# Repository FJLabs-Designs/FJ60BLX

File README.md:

# FJ60BLX Bluetooth 60% Mechanical Keyboard PCB

The following repository will hold the design files of the FJ60BLX Bluetooth Mechanical Keyboard PCB. This is designed to be a living repository and design files in this repository will be continually updated as the board iterates and changes.

## About this Repository

This repository contains rolling updates to the FJ60BLX Bluetooth PCB. Included are the base Eagle files (Board File, Schematic, and CAM Processor Job), the associated Gerber files for that revision, and the associated Bills of Materials. Each of these files will be segregated into their respective versions that are date-coded with the day of export. 

## Eagle Files

The core of this repository are the bare Eagle files. These files are the basis for the Gerber exports. **When using the eagle files, please remove the FJLabs and FJ60BLX branding.**

## Gerber Files

Included are the Gerber Files for manufacturing. These should be available in 5.6 format for all copper layers, and 4.5 format for all drills. Your PCB manufacturer requires these files to create the PCB itself. Additionally, included in the Gerber files are the relevant Pick and Place Coordinate/Centroid files which are needed for PCBA. 

## BOM Files

The included BOM files are available as Excel spreadsheets with LCSC links whereever possible. Certain components are not available from LCSC and must be purchased either directly from the manufacturer or from an authorized components distributor. 

## Renders

This folder includes a master list of all renders that have been sent to subscribers of the FJ60BLX mailing list and are date-coded. 

## Manufacturing Information

### Bluetooth Module

The PCB uses the MDBT40-256v3 Bluetooth module designed and manufactured by Raytac. This module must be programmed with the Adafruit Bluefruit SPI Friend firmware for compatibility with QMK. The relevant firmware has not been included as it is property of Adafruit and its respective company. However, this firmware is available for free open-source on GitHub (link not provided). Additionally, a SoftDevice file is required for programming of the bare Bluetooth module, which is included in the Adafruit repository for the Nordic 51822 chipset. 

Instructions are not included for programming the Bluetooth module over SWD, as it is more productive to purchase such modules pre-programmed directly from the manufacturer. The difference in cost between a programmed and unprogrammed module is negligble and therefore, for production, it is *highly recommended* to purchase preflashed chips.

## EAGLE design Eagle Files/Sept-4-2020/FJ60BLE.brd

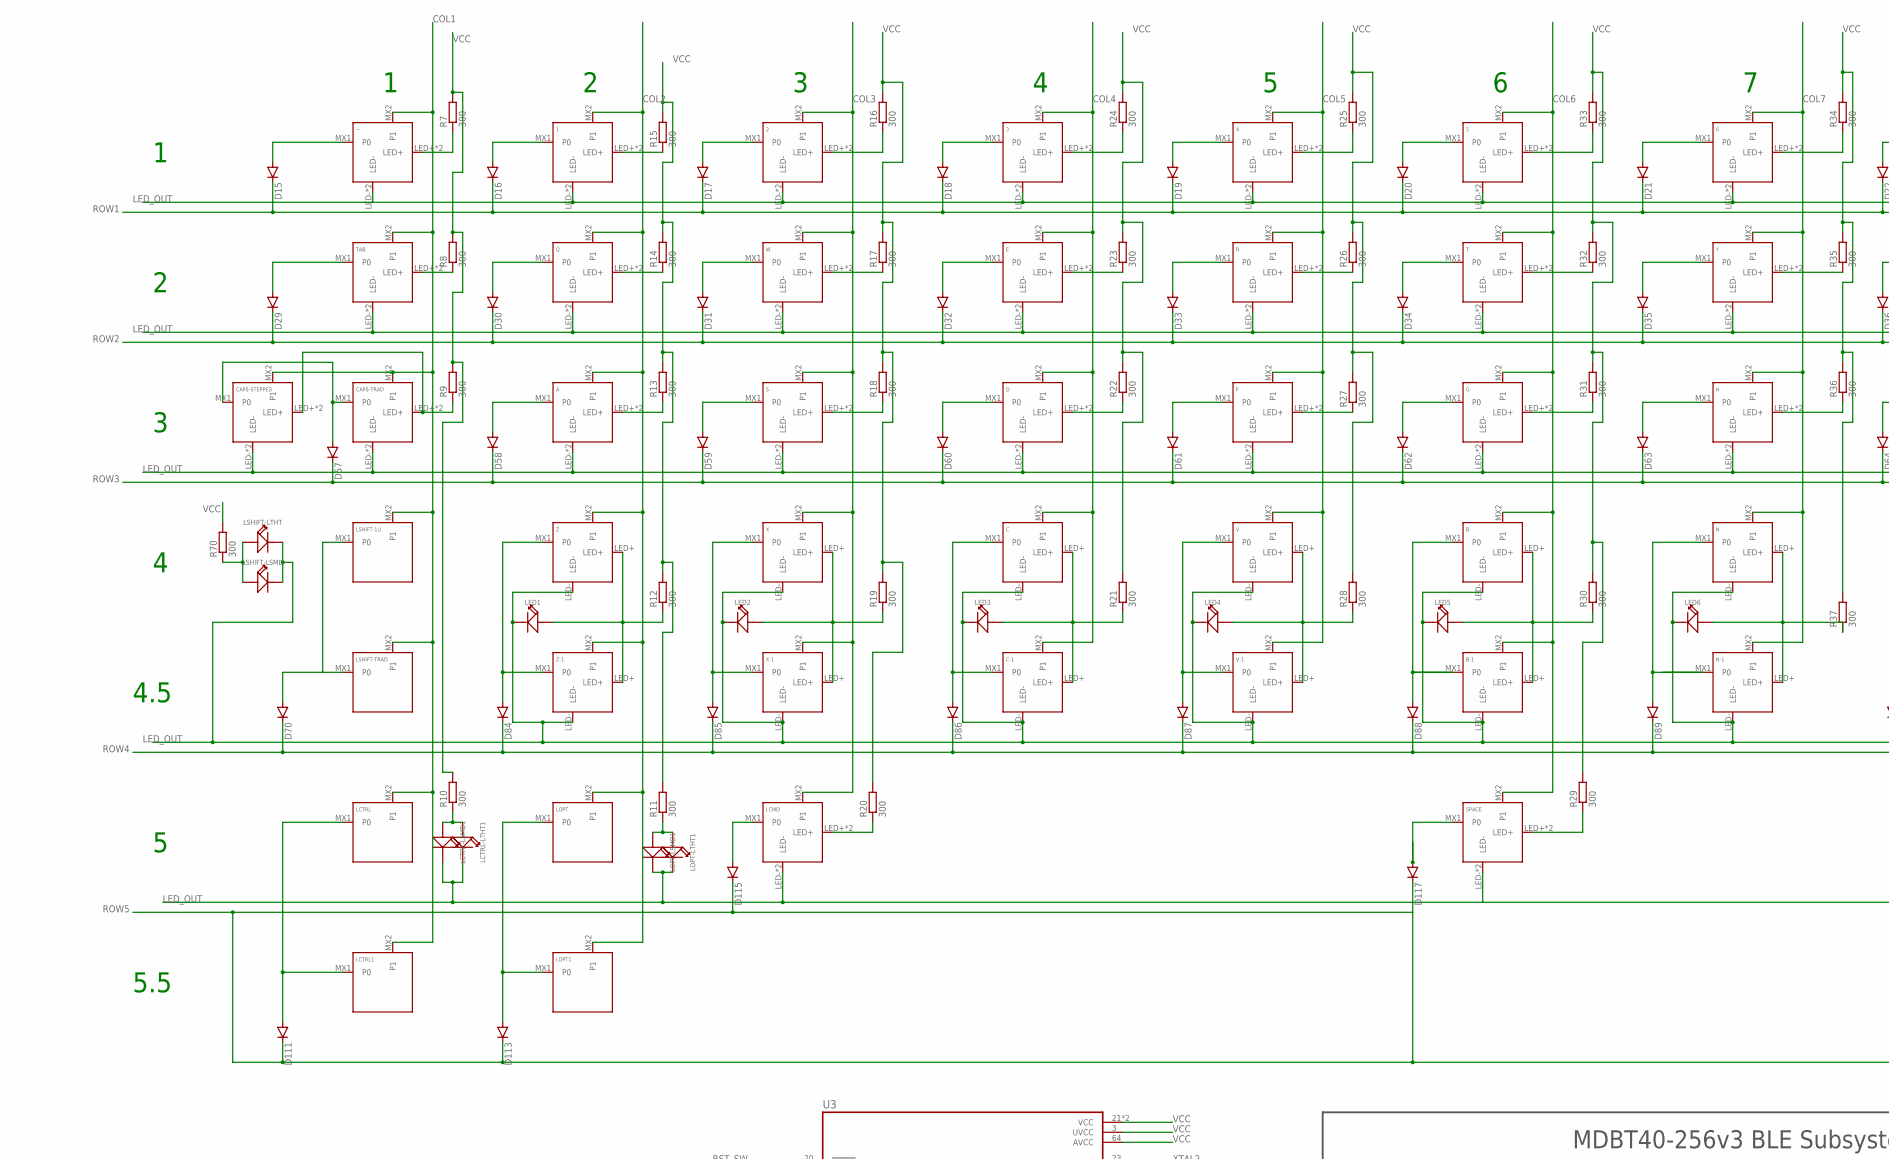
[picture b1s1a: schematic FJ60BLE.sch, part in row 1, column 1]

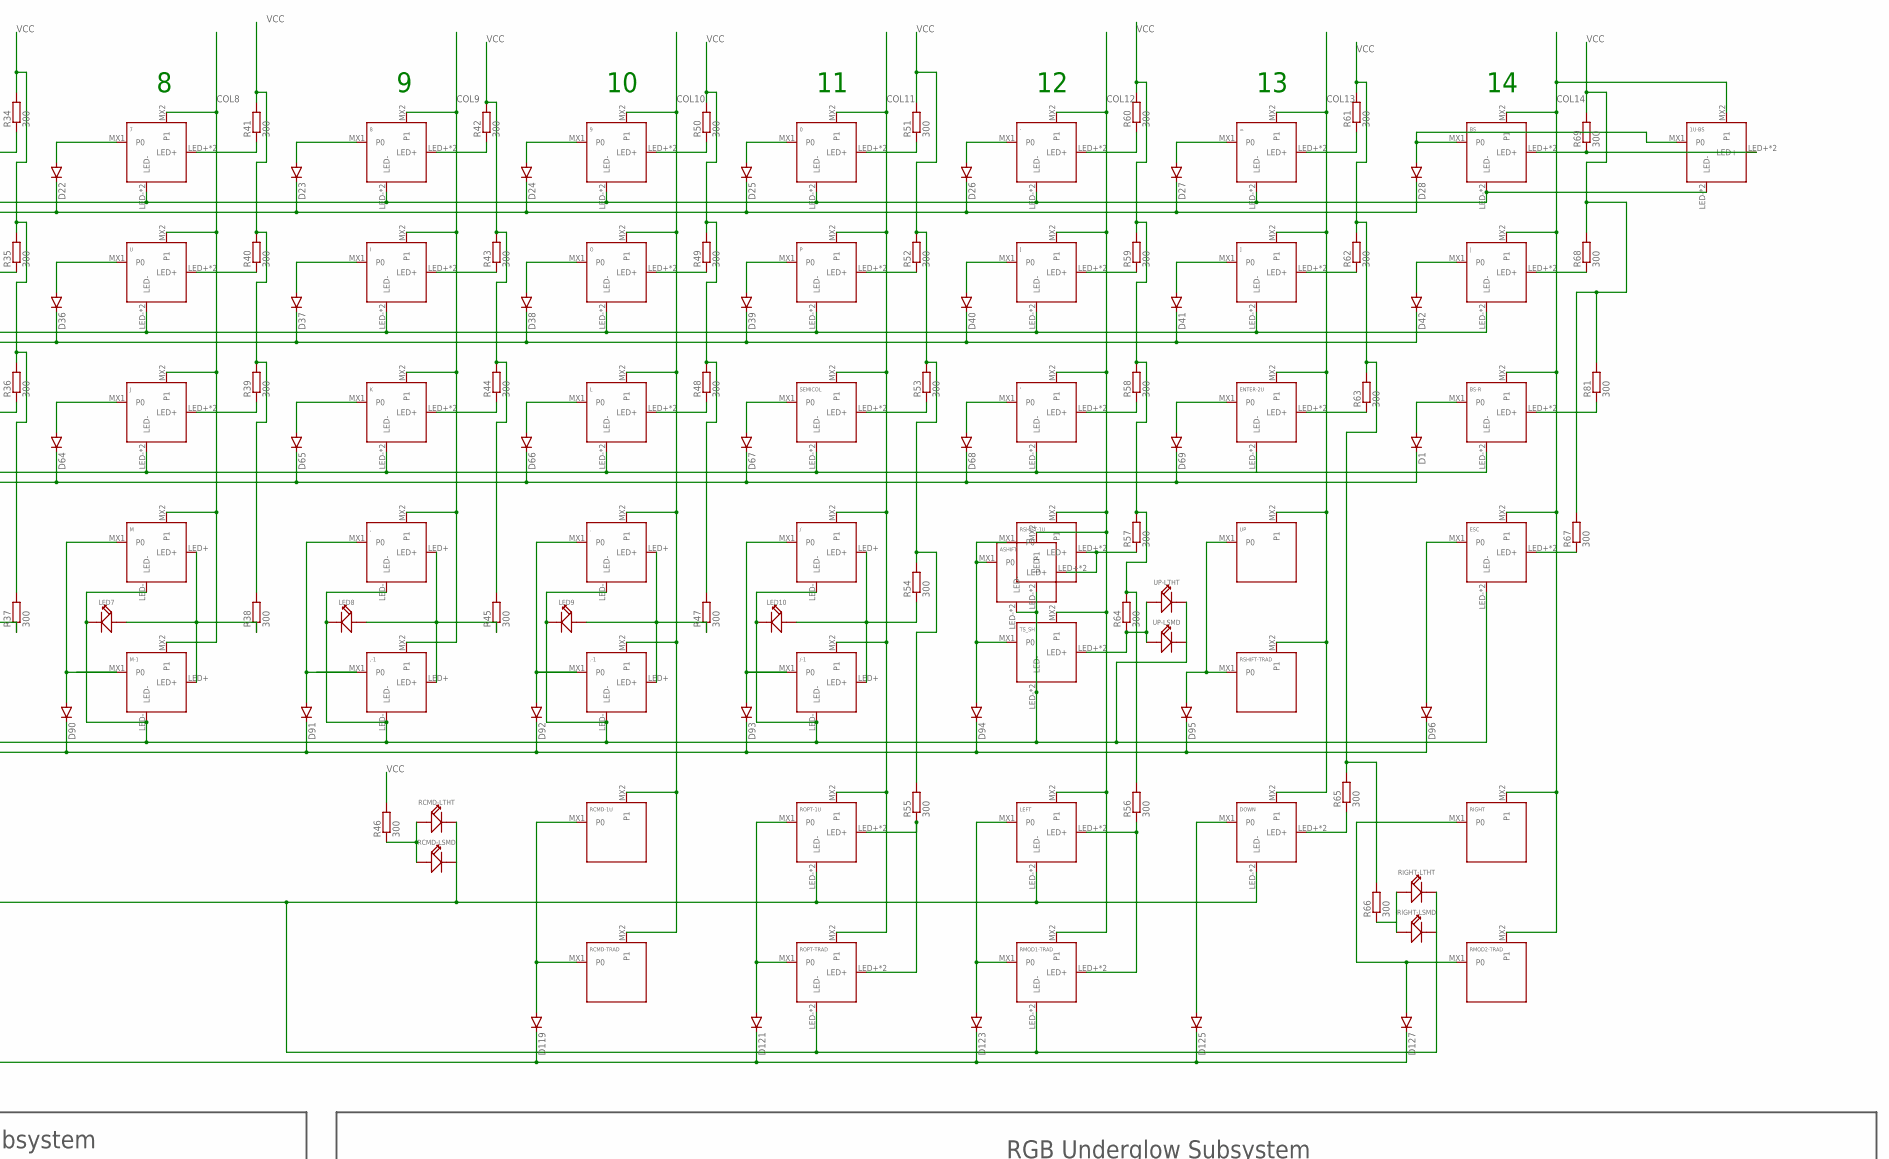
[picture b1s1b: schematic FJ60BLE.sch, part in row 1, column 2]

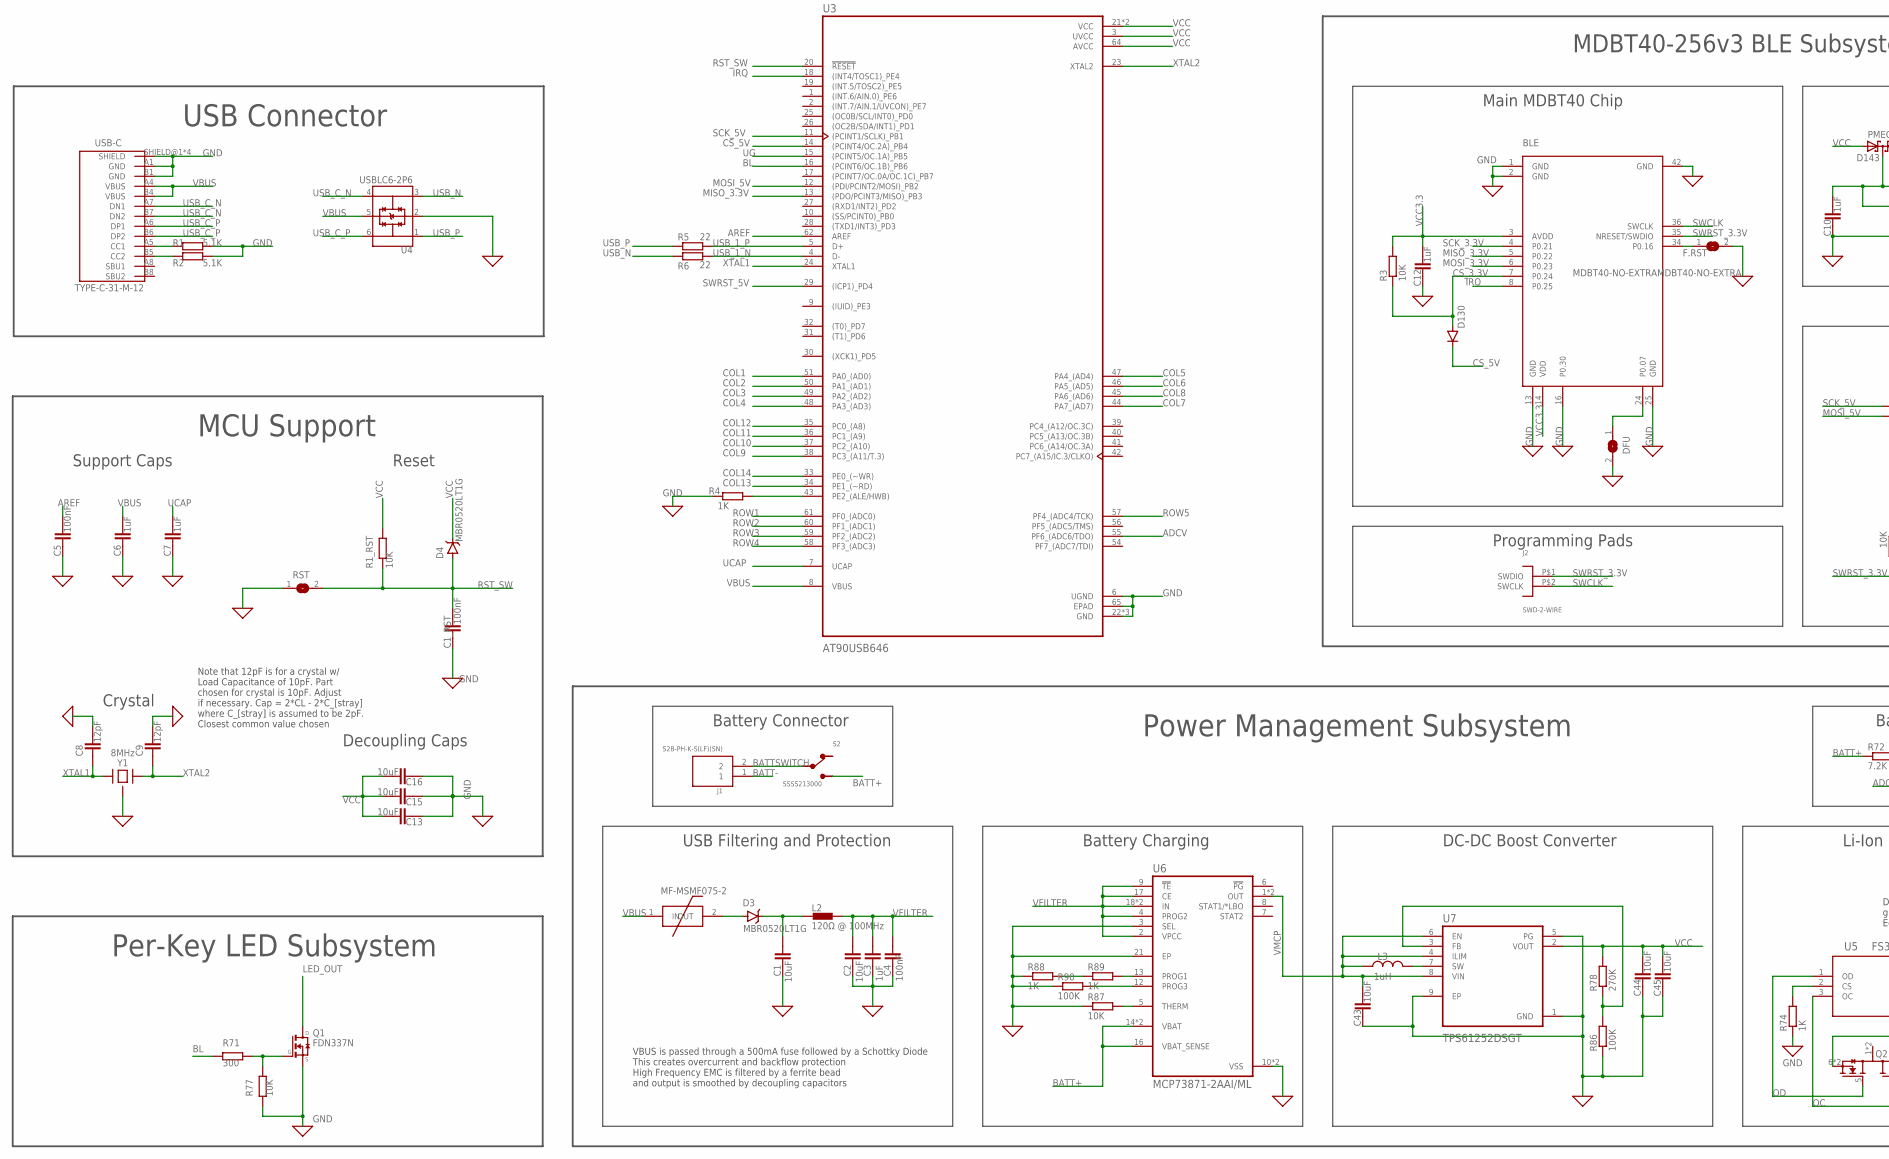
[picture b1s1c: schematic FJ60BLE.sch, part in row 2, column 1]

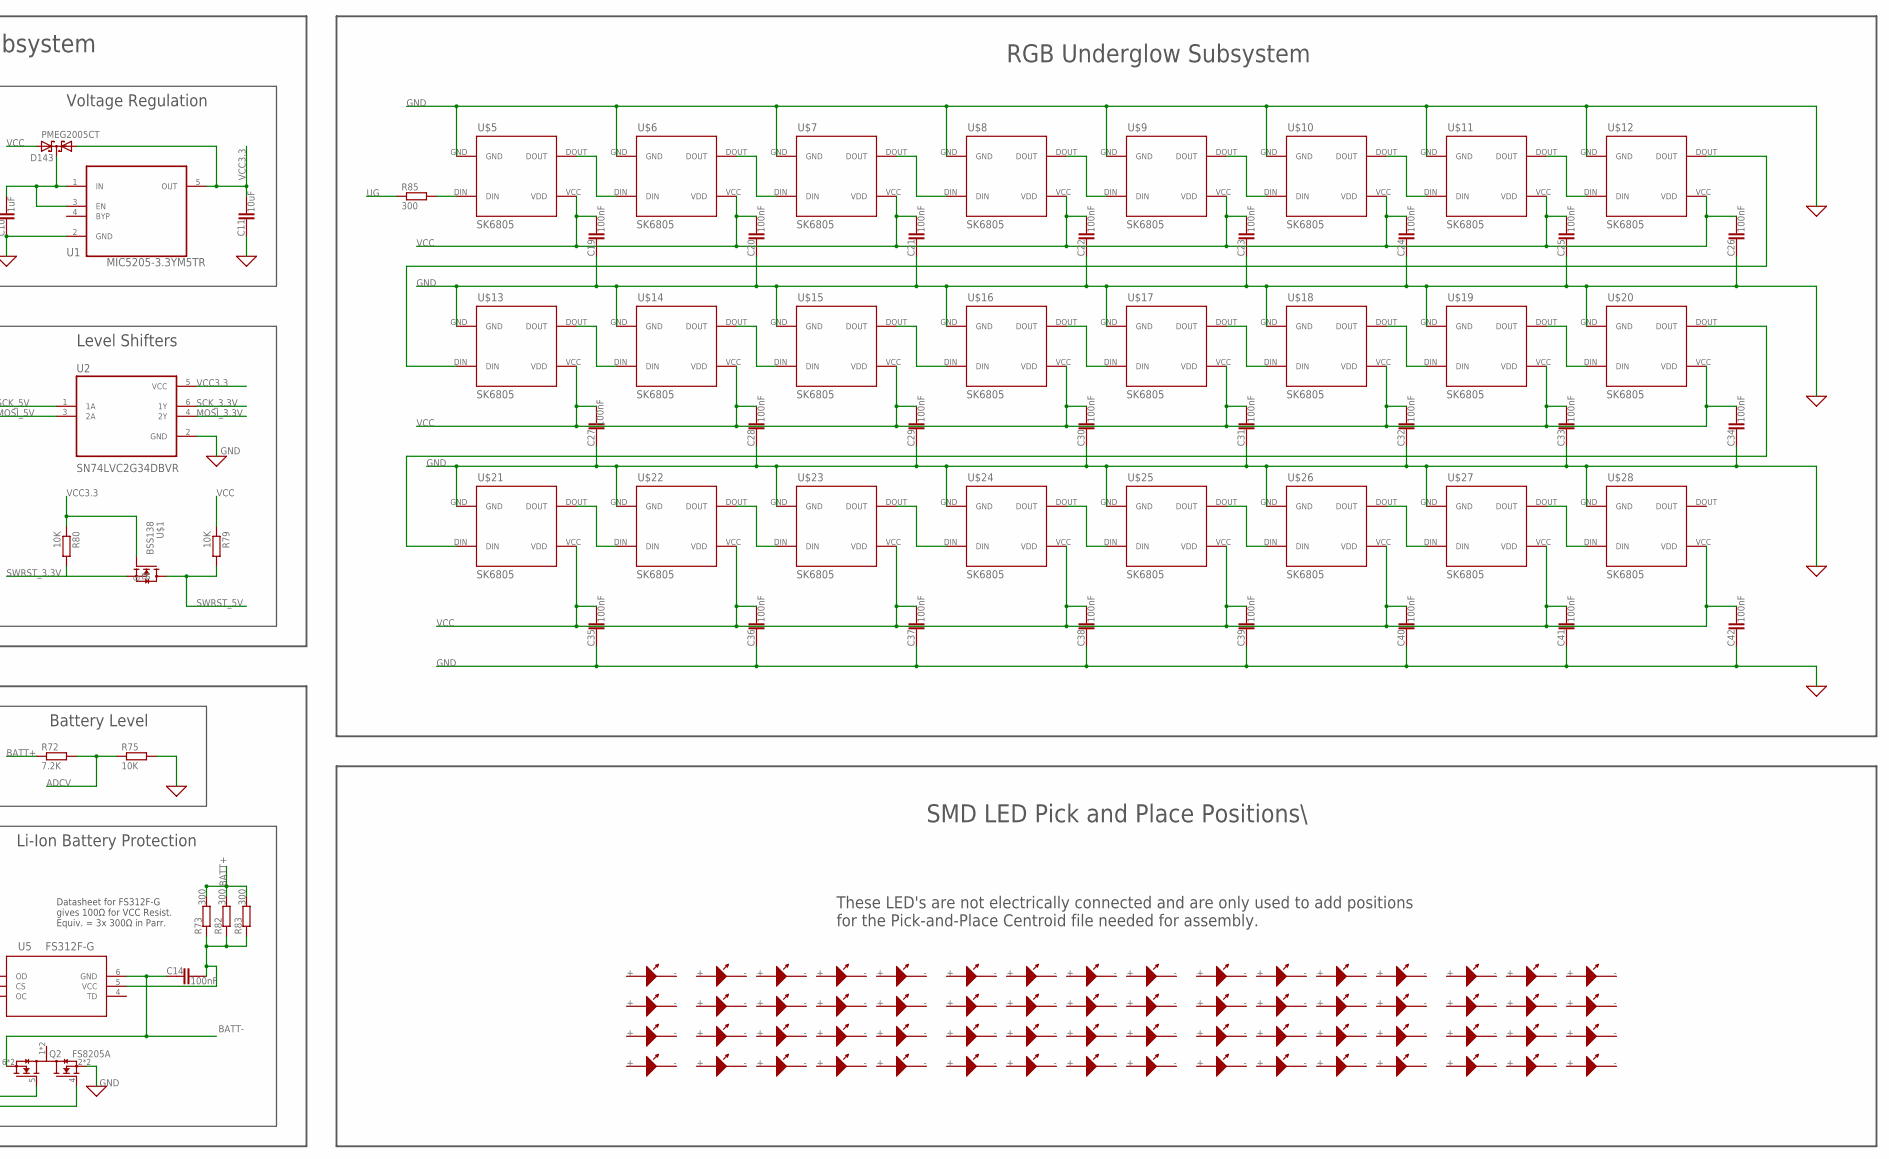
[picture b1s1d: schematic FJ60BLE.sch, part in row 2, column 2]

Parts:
0, 1, 1U-BS, 2, 3, 4, 5, 6, 7, 8, 9: KEYSWITCH-THTSMDLED-MX-1U-THTSMDLED; MX-1U-THTSMDLED
': KEYSWITCH-THTSMDLED-MX-1U-THTSMDLED; MX-1U-THTSMDLED
,: KEYSWITCH-LED-MX-1U-LED; MX-1U-LED
,-1: KEYSWITCH-LED-MX-1U-LED; MX-1U-LED
-: KEYSWITCH-THTSMDLED-MX-1U-THTSMDLED; MX-1U-THTSMDLED
., .-1: KEYSWITCH-LED-MX-1U-LED; MX-1U-LED
/: KEYSWITCH-LED-MX-1U-LED; MX-1U-LED
/-1: KEYSWITCH-LED-MX-1U-LED; MX-1U-LED
=: KEYSWITCH-THTSMDLED-MX-1U-THTSMDLED; MX-1U-THTSMDLED
A: KEYSWITCH-THTSMDLED-MX-1U-THTSMDLED; MX-1U-THTSMDLED
ASHIFT: KEYSWITCH-THTSMDLED-MX-1U-THTSMDLED; MX-1U-THTSMDLED
B: KEYSWITCH-LED-MX-1U-LED; MX-1U-LED
B-1: KEYSWITCH-LED-MX-1U-LED; MX-1U-LED
BLE: MDBT40-NO-EXTRAMDBT40-NO-EXTRA; MDBT40-NO-EXTRA
BS: KEYSWITCH-THTSMDLED-MX-2U-THTSMDLED-FLIPPED; MX-2U-THTSMDLED-FLIPPED
BS-R: KEYSWITCH-THTSMDLED-MX-1U-THTSMDLED; MX-1U-THTSMDLED
C: KEYSWITCH-LED-MX-1U-LED; MX-1U-LED
C1, C2, C11, C13, C15, C16, C43, C44, C45: 10uF; C0603
C1_RST, C4, C5, C14, C19, C20, C21, C22, C23, C24, C25, C26, C27, C28, C29, C30, C31, C32, C33, C34, C35, C36, C37, C38, C39, C40, C41, C42: 100nF; C0603
C3, C6, C7, C10, C12: 1uF; C0603
C8, C9: 12pF; C0603
C-1: KEYSWITCH-LED-MX-1U-LED; MX-1U-LED
CAPS-STEPPED: KEYSWITCH-THTSMDLED-MX-1U-THTSMDLED; MX-1U-THTSMDLED
CAPS-TRAD: KEYSWITCH-THTSMDLED-MX-1U-THTSMDLED; MX-1U-THTSMDLED
D: KEYSWITCH-THTSMDLED-MX-1U-THTSMDLED; MX-1U-THTSMDLED
D1, D15, D16, D17, D18, D19, D20, D21, D22, D23, D24, D25, D26, D27, D28, D29, D30, D31, D32, D33, D34, D35, D36, D37, D38, D39, D40, D41, D42, D57, D58, D59, D60, D61, D62, D63, D64, D65, D66, D67, D68, D69, D70, D84, D85, D86, D87, D88, D89, D90, D91, D92, D93, D94, D95, D96, D111, D113, D115, D117, D119, D121, D123, D125, D127, D130: DIODE-SOD323-R; SOD323-R
D3, D4: MBR0520LT1G; SOD-123
D143: PMEG2005CT; SOT23
DFU: SJ
DOWN: KEYSWITCH-THTSMDLED-MX-1U-THTSMDLED; MX-1U-THTSMDLED
E: KEYSWITCH-THTSMDLED-MX-1U-THTSMDLED; MX-1U-THTSMDLED
ENTER-2U: KEYSWITCH-THTSMDLED-MX-2U-THTSMDLED-FLIPPED; MX-2U-THTSMDLED-FLIPPED
ESC: KEYSWITCH-THTSMDLED-MX-1U-THTSMDLED; MX-1U-THTSMDLED
F: KEYSWITCH-THTSMDLED-MX-1U-THTSMDLED; MX-1U-THTSMDLED
F1: MF-MSMF075-2; CAPC1210X112N
F.RST: SJ
G: KEYSWITCH-THTSMDLED-MX-1U-THTSMDLED; MX-1U-THTSMDLED
H: KEYSWITCH-THTSMDLED-MX-1U-THTSMDLED; MX-1U-THTSMDLED
I: KEYSWITCH-THTSMDLED-MX-1U-THTSMDLED; MX-1U-THTSMDLED
J: KEYSWITCH-THTSMDLED-MX-1U-THTSMDLED; MX-1U-THTSMDLED
J1: S2B-PH-K-S(LF)(SN); JST_S2B-PH-K-S(LF)(SN)
J2: SWD-2-WIRE; HEADER-2X1-2.54
K: KEYSWITCH-THTSMDLED-MX-1U-THTSMDLED; MX-1U-THTSMDLED
L: KEYSWITCH-THTSMDLED-MX-1U-THTSMDLED; MX-1U-THTSMDLED
L2: 120Ω @ 100MHz; 0402
L3: 1uH; INDC2009X120
LCMD: KEYSWITCH-THTSMDLED-MX-1U-THTSMDLED; MX-1U-THTSMDLED
LCTRL, LCTRL1: KEYSWITCH-PLAIN-MX-1U; MX-1U
LCTRL-LSMD1: LED-2-PLACEMENT-SMD; SMD-LED-UNIVERSAL-2-PLACEMENTS
LCTRL-LTHT1: LED-2-PLACEMENT-THT; LED-THT-2PLACEMENT
LED1, LED2, LED3, LED4, LED5, LED6, LED7, LED8, LED9, LED10: LED-4-PLACEMENT-SMD; SMD-LED-UNIVERSAL-DUAL
LEFT: KEYSWITCH-THTSMDLED-MX-1U-THTSMDLED; MX-1U-THTSMDLED
LOPT, LOPT1: KEYSWITCH-PLAIN-MX-1U; MX-1U
LOPT-LSMD1: LED-2-PLACEMENT-SMD; SMD-LED-UNIVERSAL-2-PLACEMENTS
LOPT-LTHT1: LED-2-PLACEMENT-THT; LED-THT-2PLACEMENT
LSHIFT-1U: KEYSWITCH-PLAIN-MX-2U-FLIPPED; MX-2U-FLIPPED
LSHIFT-LSMD: LED-2-PLACEMENT-SMD; SMD-LED-UNIVERSAL-2-PLACEMENTS
LSHIFT-LTHT: LED-2-PLACEMENT-THT; LED-THT-2PLACEMENT
LSHIFT-TRAD: KEYSWITCH-PLAIN-MX-2U-FLIPPED; MX-2U-FLIPPED
M: KEYSWITCH-LED-MX-1U-LED; MX-1U-LED
M-1: KEYSWITCH-LED-MX-1U-LED; MX-1U-LED
N: KEYSWITCH-LED-MX-1U-LED; MX-1U-LED
N-1: KEYSWITCH-LED-MX-1U-LED; MX-1U-LED
O: KEYSWITCH-THTSMDLED-MX-1U-THTSMDLED; MX-1U-THTSMDLED
P: KEYSWITCH-THTSMDLED-MX-1U-THTSMDLED; MX-1U-THTSMDLED
Q: KEYSWITCH-THTSMDLED-MX-1U-THTSMDLED; MX-1U-THTSMDLED
Q1: FDN337N; SSOT-3
Q2: FS8205A; SOP65P640X120-8N
R: KEYSWITCH-THTSMDLED-MX-1U-THTSMDLED; MX-1U-THTSMDLED
R1, R2: 5.1K; R0402
R1_RST, R3, R75, R77, R79, R80, R87: 10K; R0402
R4, R74, R88, R89: 1K; R0402
R5, R6: 22; R0402
R7, R8, R9, R10, R11, R12, R13, R14, R15, R16, R17, R18, R19, R20, R21, R22, R23, R24, R25, R26, R27, R28, R29, R30, R31, R32, R33, R34, R35, R36, R37, R38, R39, R40, R41, R42, R43, R44, R45, R46, R47, R48, R49, R50, R51, R52, R53, R54, R55, R56, R57, R58, R59, R60, R61, R62, R63, R64, R65, R66, R67, R68, R69, R70, R71, R73, R81, R82, R83, R85: 300; R0603
R72: 7.2K; R0402
R78: 270K; R0402
R86, R90: 100K; R0402
RCMD-1U: KEYSWITCH-PLAIN-MX-1U; MX-1U
RCMD-LSMD: LED-2-PLACEMENT-SMD; SMD-LED-UNIVERSAL-2-PLACEMENTS
RCMD-LTHT: LED-2-PLACEMENT-THT; LED-THT-2PLACEMENT
RCMD-TRAD: KEYSWITCH-PLAIN-MX-1U; MX-1U
RIGHT: KEYSWITCH-PLAIN-MX-1U; MX-1U
RIGHT-LSMD: LED-2-PLACEMENT-SMD; SMD-LED-UNIVERSAL-2-PLACEMENTS
RIGHT-LTHT: LED-2-PLACEMENT-THT; LED-THT-2PLACEMENT
RMOD1-TRAD: KEYSWITCH-THTSMDLED-MX-1U-THTSMDLED; MX-1U-THTSMDLED
RMOD2-TRAD: KEYSWITCH-PLAIN-MX-1U; MX-1U
ROPT-1U: KEYSWITCH-THTSMDLED-MX-1U-THTSMDLED; MX-1U-THTSMDLED
ROPT-TRAD: KEYSWITCH-THTSMDLED-MX-1U-THTSMDLED; MX-1U-THTSMDLED
RSHIFT-1U: KEYSWITCH-THTSMDLED-MX-1U-THTSMDLED; MX-1U-THTSMDLED
RSHIFT-TRAD: KEYSWITCH-PLAIN-MX-1U; MX-1U
RST: SJ
S: KEYSWITCH-THTSMDLED-MX-1U-THTSMDLED; MX-1U-THTSMDLED
S2: SSSS213000
SEMICOL: KEYSWITCH-THTSMDLED-MX-1U-THTSMDLED; MX-1U-THTSMDLED
SPACE: KEYSWITCH-THTSMDLED-MX-6.25U-THTSMDLED; MX-6.25U-THTSMDLED
T: KEYSWITCH-THTSMDLED-MX-1U-THTSMDLED; MX-1U-THTSMDLED
TAB: KEYSWITCH-THTSMDLED-MX-1U-THTSMDLED; MX-1U-THTSMDLED
TS_SH: KEYSWITCH-THTSMDLED-MX-1U-THTSMDLED; MX-1U-THTSMDLED
U: KEYSWITCH-THTSMDLED-MX-1U-THTSMDLED; MX-1U-THTSMDLED
U1: MIC5205-3.3YM5TR; SOT95P280X130-5N
U2: SN74LVC2G34DBVR; SOT95P280X145-6N
U3: AT90USB646; QFN50P900X900X100-65N
U4: USBLC6-2P6; SOT50P160X60-6N
U5: FS312F-G
U6: MCP73871-2AAI/ML; QFN50P400X400X100-21N
U7: TPS61252DSGT; SON50P200X200X80-9N
U$1: BSS138; SOT-23
U$5, U$6, U$7, U$8, U$9, U$10, U$11, U$12, U$13, U$14, U$15, U$16, U$17, U$18, U$19, U$20, U$21, U$22, U$23, U$24, U$25, U$26, U$27, U$28: SK6805
U$29, U$30, U$31, U$32, U$33, U$34, U$35, U$36, U$37, U$38, U$39, U$40, U$41, U$42, U$43, U$44, U$45, U$46, U$47, U$48, U$49, U$50, U$51, U$52, U$53, U$54, U$55, U$56, U$57, U$58, U$59, U$60, U$61, U$62, U$63, U$64, U$65, U$66, U$67, U$68, U$69, U$70, U$71, U$72, U$73, U$74, U$75, U$76, U$77, U$78, U$79, U$80, U$81, U$82, U$83, U$84, U$85, U$86, U$87, U$88, U$89, U$90, U$91, U$92: LED-0805; LED0805
UP: KEYSWITCH-PLAIN-MX-1U; MX-1U
UP-LSMD: LED-2-PLACEMENT-SMD; SMD-LED-UNIVERSAL-2-PLACEMENTS
UP-LTHT: LED-2-PLACEMENT-THT; LED-THT-2PLACEMENT
USB-C: USB-C; TYPE-C-31-M-12
V: KEYSWITCH-LED-MX-1U-LED; MX-1U-LED
V-1: KEYSWITCH-LED-MX-1U-LED; MX-1U-LED
W: KEYSWITCH-THTSMDLED-MX-1U-THTSMDLED; MX-1U-THTSMDLED
X: KEYSWITCH-LED-MX-1U-LED; MX-1U-LED
X-1: KEYSWITCH-LED-MX-1U-LED; MX-1U-LED
Y: KEYSWITCH-THTSMDLED-MX-1U-THTSMDLED; MX-1U-THTSMDLED
Y1: 8MHz; CRYSTAL-3.2X2.5
Z: KEYSWITCH-LED-MX-1U-LED; MX-1U-LED
Z-1: KEYSWITCH-LED-MX-1U-LED; MX-1U-LED
[: KEYSWITCH-THTSMDLED-MX-1U-THTSMDLED; MX-1U-THTSMDLED
]: KEYSWITCH-THTSMDLED-MX-1U-THTSMDLED; MX-1U-THTSMDLED
|: KEYSWITCH-THTSMDLED-MX-1U-THTSMDLED; MX-1U-THTSMDLED
~: KEYSWITCH-THTSMDLED-MX-1U-THTSMDLED; MX-1U-THTSMDLED

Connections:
ADCV: R72.2, R75.1, U3.55 (PF6_(ADC6/TDO))
AREF: C5.2, U3.62 (AREF)
BATT+: R72.1, R73.2, R82.2, R83.2, S2.P3 (3), U6.14 (VBAT), U6.15 (VBAT), U6.16 (VBAT_SENSE)
BATT-: C14.1, J1.1, Q2.6 (S2), Q2.7 (S2), U5.6 (GND)
BATTSWITCH: J1.2, S2.P2 (2)
BL: R71.1, U3.16 ((PCINT6/OC.1B)_PB6)
COL1: CAPS-STEPPED.MX2 (P1), CAPS-TRAD.MX2 (P1), LCTRL.MX2 (P1), LCTRL1.MX2 (P1), LSHIFT-1U.MX2 (P1), LSHIFT-TRAD.MX2 (P1), TAB.MX2 (P1), U3.51 (PA0_(AD0)), ~.MX2 (P1)
COL2: 1.MX2 (P1), A.MX2 (P1), LOPT.MX2 (P1), LOPT1.MX2 (P1), Q.MX2 (P1), U3.50 (PA1_(AD1)), Z.MX2 (P1), Z-1.MX2 (P1)
COL3: 2.MX2 (P1), LCMD.MX2 (P1), S.MX2 (P1), U3.49 (PA2_(AD2)), W.MX2 (P1), X.MX2 (P1), X-1.MX2 (P1)
COL4: 3.MX2 (P1), C.MX2 (P1), C-1.MX2 (P1), D.MX2 (P1), E.MX2 (P1), U3.48 (PA3_(AD3))
COL5: 4.MX2 (P1), F.MX2 (P1), R.MX2 (P1), U3.47 (PA4_(AD4)), V.MX2 (P1), V-1.MX2 (P1)
COL6: 5.MX2 (P1), B.MX2 (P1), B-1.MX2 (P1), G.MX2 (P1), SPACE.MX2 (P1), T.MX2 (P1), U3.46 (PA5_(AD5))
COL7: 6.MX2 (P1), H.MX2 (P1), N.MX2 (P1), N-1.MX2 (P1), U3.44 (PA7_(AD7)), Y.MX2 (P1)
COL8: 7.MX2 (P1), J.MX2 (P1), M.MX2 (P1), M-1.MX2 (P1), U.MX2 (P1), U3.45 (PA6_(AD6))
COL9: 8.MX2 (P1), ,.MX2 (P1), ,-1.MX2 (P1), I.MX2 (P1), K.MX2 (P1), U3.38 (PC3_(A11/T.3))
COL10: 9.MX2 (P1), ..MX2 (P1), .-1.MX2 (P1), L.MX2 (P1), O.MX2 (P1), RCMD-1U.MX2 (P1), RCMD-TRAD.MX2 (P1), U3.37 (PC2_(A10))
COL11: 0.MX2 (P1), /.MX2 (P1), /-1.MX2 (P1), P.MX2 (P1), ROPT-1U.MX2 (P1), ROPT-TRAD.MX2 (P1), SEMICOL.MX2 (P1), U3.36 (PC1_(A9))
COL12: '.MX2 (P1), -.MX2 (P1), ASHIFT.MX2 (P1), LEFT.MX2 (P1), RMOD1-TRAD.MX2 (P1), RSHIFT-1U.MX2 (P1), TS_SH.MX2 (P1), U3.35 (PC0_(A8)), [.MX2 (P1)
COL13: =.MX2 (P1), DOWN.MX2 (P1), ENTER-2U.MX2 (P1), RSHIFT-TRAD.MX2 (P1), U3.34 (PE1_(~RD)), UP.MX2 (P1), ].MX2 (P1)
COL14: 1U-BS.MX2 (P1), BS.MX2 (P1), BS-R.MX2 (P1), ESC.MX2 (P1), RIGHT.MX2 (P1), RMOD2-TRAD.MX2 (P1), U3.33 (PE0_(~WR)), |.MX2 (P1)
CS_3.3V: BLE.7 (P0.24), D130.A, R3.1
CS_5V: D130.C, U3.14 ((PCINT4/OC.2A)_PB4)
GND: BLE.1 (GND), BLE.2 (GND), BLE.13 (GND), BLE.16 (P0.30), BLE.25 (GND), BLE.42 (GND), C1.1, C1_RST.1, C2.1, C3.1, C4.1, C5.1, C6.1, C7.1, C8.2, C9.2, C10.1, C11.1, C12.1, C13.1, C15.1, C16.1, C19.1, C20.1, C21.1, C22.1, C23.1, C24.1, C25.1, C26.1, C27.1, C28.1, C29.1, C30.1, C31.1, C32.1, C33.1, C34.1, C35.1, C36.1, C37.1, C38.1, C39.1, C40.1, C41.1, C42.1, C43.1, C44.1, C45.1, DFU.2, F.RST.2, Q1.2 (S), Q2.2 (S1), Q2.3 (S1), R1.1, R2.2, R4.1, R74.1, R75.2, R77.1, R86.1, R87.1, R88.1, R90.1, RST.1, U1.2 (GND), U2.2 (GND), U3.6 (UGND), U3.22 (GND), U3.53 (GND), U3.63 (GND), U3.65 (EPAD), U4.2 (GND), U6.3 (SEL), U6.10 (VSS), U6.11 (VSS), U6.21 (EP), U7.1 (GND), U7.5 (PG), U7.9 (EP), U$5.GND, U$6.GND, U$7.GND, U$8.GND, U$9.GND, U$10.GND, U$11.GND, U$12.GND, U$13.GND, U$14.GND, U$15.GND, U$16.GND, U$17.GND, U$18.GND, U$19.GND, U$20.GND, U$21.GND, U$22.GND, U$23.GND, U$24.GND, U$25.GND, U$26.GND, U$27.GND, U$28.GND, USB-C.A1 (GND), USB-C.B1 (GND), USB-C.SHIELD@1 (SHIELD), USB-C.SHIELD@2 (SHIELD), USB-C.SHIELD@3 (SHIELD), USB-C.SHIELD@4 (SHIELD), Y1.2 (GND), Y1.4 (GND)
IRQ: BLE.8 (P0.25), U3.18 ((INT4/TOSC1)_PE4)
LED_OUT: 0.LED-, 0.SMDLED- (LED-), 1.LED-, 1.SMDLED- (LED-), 1U-BS.LED-, 1U-BS.SMDLED- (LED-), 2.LED-, 2.SMDLED- (LED-), 3.LED-, 3.SMDLED- (LED-), 4.LED-, 4.SMDLED- (LED-), 5.LED-, 5.SMDLED- (LED-), 6.LED-, 6.SMDLED- (LED-), 7.LED-, 7.SMDLED- (LED-), 8.LED-, 8.SMDLED- (LED-), 9.LED-, 9.SMDLED- (LED-), '.LED-, '.SMDLED- (LED-), ,.LED-, ,-1.LED-, -.LED-, -.SMDLED- (LED-), ..LED-, .-1.LED-, /.LED-, /-1.LED-, =.LED-, =.SMDLED- (LED-), A.LED-, A.SMDLED- (LED-), ASHIFT.LED-, ASHIFT.SMDLED- (LED-), B.LED-, B-1.LED-, BS.LED-, BS.SMDLED- (LED-), BS-R.LED-, BS-R.SMDLED- (LED-), C.LED-, C-1.LED-, CAPS-STEPPED.LED-, CAPS-STEPPED.SMDLED- (LED-), CAPS-TRAD.LED-, CAPS-TRAD.SMDLED- (LED-), D.LED-, D.SMDLED- (LED-), DOWN.LED-, DOWN.SMDLED- (LED-), E.LED-, E.SMDLED- (LED-), ENTER-2U.LED-, ENTER-2U.SMDLED- (LED-), ESC.LED-, ESC.SMDLED- (LED-), F.LED-, F.SMDLED- (LED-), G.LED-, G.SMDLED- (LED-), H.LED-, H.SMDLED- (LED-), I.LED-, I.SMDLED- (LED-), J.LED-, J.SMDLED- (LED-), K.LED-, K.SMDLED- (LED-), L.LED-, L.SMDLED- (LED-), LCMD.LED-, LCMD.SMDLED- (LED-), LCTRL-LSMD1.MINUS1 (MINUS), LCTRL-LSMD1.MINUS2 (MINUS), LCTRL-LTHT1.1 (MINUS), LED1.MINUS1 (MINUS), LED1.MINUS2 (MINUS), LED2.MINUS1 (MINUS), LED2.MINUS2 (MINUS), LED3.MINUS1 (MINUS), LED3.MINUS2 (MINUS), LED4.MINUS1 (MINUS), LED4.MINUS2 (MINUS), LED5.MINUS1 (MINUS), LED5.MINUS2 (MINUS), LED6.MINUS1 (MINUS), LED6.MINUS2 (MINUS), LED7.MINUS1 (MINUS), LED7.MINUS2 (MINUS), LED8.MINUS1 (MINUS), LED8.MINUS2 (MINUS), LED9.MINUS1 (MINUS), LED9.MINUS2 (MINUS), LED10.MINUS1 (MINUS), LED10.MINUS2 (MINUS), LEFT.LED-, LEFT.SMDLED- (LED-), LOPT-LSMD1.MINUS1 (MINUS), LOPT-LSMD1.MINUS2 (MINUS), LOPT-LTHT1.1 (MINUS), LSHIFT-LSMD.MINUS1 (MINUS), LSHIFT-LSMD.MINUS2 (MINUS), LSHIFT-LTHT.1 (MINUS), M.LED-, M-1.LED-, N.LED-, N-1.LED-, O.LED-, O.SMDLED- (LED-), P.LED-, P.SMDLED- (LED-), Q.LED-, Q.SMDLED- (LED-), Q1.3 (D), R.LED-, R.SMDLED- (LED-), RCMD-LSMD.MINUS1 (MINUS), RCMD-LSMD.MINUS2 (MINUS), RCMD-LTHT.1 (MINUS), RIGHT-LSMD.MINUS1 (MINUS), RIGHT-LSMD.MINUS2 (MINUS), RIGHT-LTHT.1 (MINUS), RMOD1-TRAD.LED-, RMOD1-TRAD.SMDLED- (LED-), ROPT-1U.LED-, ROPT-1U.SMDLED- (LED-), ROPT-TRAD.LED-, ROPT-TRAD.SMDLED- (LED-), RSHIFT-1U.LED-, RSHIFT-1U.SMDLED- (LED-), S.LED-, S.SMDLED- (LED-), SEMICOL.LED-, SEMICOL.SMDLED- (LED-), SPACE.LED-, SPACE.SMDLED- (LED-), T.LED-, T.SMDLED- (LED-), TAB.LED-, TAB.SMDLED- (LED-), TS_SH.LED-, TS_SH.SMDLED- (LED-), U.LED-, U.SMDLED- (LED-)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
LSHIFT-LED-ITC1: LSHIFT-LSMD.PLUS, LSHIFT-LTHT.2 (PLUS), LSHIFT-LTHT.3 (PLUS), R70.1
MISO_3.3V: BLE.5 (P0.22), U3.13 ((PDO/PCINT3/MISO)_PB3)
MOSI_3.3V: BLE.6 (P0.23), U2.4 (2Y)
MOSI_5V: U2.3 (2A), U3.12 ((PDI/PCINT2/MOSI)_PB2)
unnamed: D15.A, ~.MX1 (P0)
unnamed: 1.MX1 (P0), D16.A
unnamed: 3.MX1 (P0), D18.A
unnamed: D30.A, Q.MX1 (P0)
unnamed: D29.A, TAB.MX1 (P0)
unnamed: 4.MX1 (P0), D19.A
unnamed: D31.A, W.MX1 (P0)
unnamed: 2.MX1 (P0), D17.A
unnamed: 5.MX1 (P0), D20.A
unnamed: D32.A, E.MX1 (P0)
unnamed: 6.MX1 (P0), D21.A
unnamed: D33.A, R.MX1 (P0)
unnamed: 7.MX1 (P0), D22.A
unnamed: R1.2, USB-C.A5 (CC1)
unnamed: D34.A, T.MX1 (P0)
unnamed: 8.MX1 (P0), D23.A
unnamed: D35.A, Y.MX1 (P0)
unnamed: 9.MX1 (P0), D24.A
unnamed: D36.A, U.MX1 (P0)
unnamed: 0.MX1 (P0), D25.A
unnamed: D37.A, I.MX1 (P0)
unnamed: -.MX1 (P0), D26.A
unnamed: D38.A, O.MX1 (P0)
unnamed: =.MX1 (P0), D27.A
unnamed: D39.A, P.MX1 (P0)
unnamed: 1U-BS.MX1 (P0), BS.MX1 (P0), D28.A
unnamed: D3.A, F1.2 (OUT)
unnamed: D40.A, [.MX1 (P0)
unnamed: D41.A, ].MX1 (P0)
unnamed: D42.A, |.MX1 (P0)
unnamed: C1.2, D3.C, L2.1
unnamed: A.MX1 (P0), D58.A
unnamed: CAPS-STEPPED.MX1 (P0), CAPS-TRAD.MX1 (P0), D57.A
unnamed: D59.A, S.MX1 (P0)
unnamed: D.MX1 (P0), D60.A
unnamed: D61.A, F.MX1 (P0)
unnamed: D62.A, G.MX1 (P0)
unnamed: D63.A, H.MX1 (P0)
unnamed: D64.A, J.MX1 (P0)
unnamed: D65.A, K.MX1 (P0)
unnamed: D66.A, L.MX1 (P0)
unnamed: D67.A, SEMICOL.MX1 (P0)
unnamed: '.MX1 (P0), D68.A
unnamed: D69.A, ENTER-2U.MX1 (P0)
unnamed: D84.A, Z.MX1 (P0), Z-1.MX1 (P0)
unnamed: LED1.PLUS1 (PLUS), LED1.PLUS2 (PLUS), R12.1, Z.LED+, Z-1.LED+
unnamed: R7.1, ~.LED+, ~.SMDLED+ (LED+)
unnamed: D85.A, X.MX1 (P0), X-1.MX1 (P0)
unnamed: C.MX1 (P0), C-1.MX1 (P0), D86.A
unnamed: D87.A, V.MX1 (P0), V-1.MX1 (P0)
unnamed: B.MX1 (P0), B-1.MX1 (P0), D88.A
unnamed: D89.A, N.MX1 (P0), N-1.MX1 (P0)
unnamed: D90.A, M.MX1 (P0), M-1.MX1 (P0)
unnamed: ,.MX1 (P0), ,-1.MX1 (P0), D91.A
unnamed: D95.A, RSHIFT-TRAD.MX1 (P0), UP.MX1 (P0)
unnamed: ..MX1 (P0), .-1.MX1 (P0), D92.A
unnamed: /.MX1 (P0), /-1.MX1 (P0), D93.A
unnamed: BLE.24 (P0.07), DFU.1
unnamed: ASHIFT.MX1 (P0), D94.A, RSHIFT-1U.MX1 (P0), TS_SH.MX1 (P0)
unnamed: 2.LED+, 2.SMDLED+ (LED+), R16.1
unnamed: D96.A, ESC.MX1 (P0)
unnamed: R8.1, TAB.LED+, TAB.SMDLED+ (LED+)
unnamed: D70.A, LSHIFT-1U.MX1 (P0), LSHIFT-TRAD.MX1 (P0)
unnamed: R2.1, USB-C.B5 (CC2)
unnamed: Q1.1 (G), R71.2, R77.2
unnamed: LED2.PLUS1 (PLUS), LED2.PLUS2 (PLUS), R19.1, X.LED+, X-1.LED+
unnamed: C14.2, R73.1, R82.1, R83.1, U5.5 (VCC)
unnamed: LED4.PLUS1 (PLUS), LED4.PLUS2 (PLUS), R28.1, V.LED+, V-1.LED+
unnamed: 8.LED+, 8.SMDLED+ (LED+), R42.1
unnamed: 5.LED+, 5.SMDLED+ (LED+), R33.1
unnamed: D111.A, LCTRL.MX1 (P0), LCTRL1.MX1 (P0)
unnamed: LOPT-LSMD1.PLUS, LOPT-LTHT1.2 (PLUS), LOPT-LTHT1.3 (PLUS), R11.1
unnamed: R74.2, U5.2 (CS)
unnamed: R78.1, R86.2, U7.3 (FB)
unnamed: LCTRL-LSMD1.PLUS, LCTRL-LTHT1.2 (PLUS), LCTRL-LTHT1.3 (PLUS), R10.1
unnamed: B.LED+, B-1.LED+, LED5.PLUS1 (PLUS), LED5.PLUS2 (PLUS), R30.1
unnamed: LED6.PLUS1 (PLUS), LED6.PLUS2 (PLUS), N.LED+, N-1.LED+, R37.1
unnamed: LED7.PLUS1 (PLUS), LED7.PLUS2 (PLUS), M.LED+, M-1.LED+, R38.1
unnamed: ,.LED+, ,-1.LED+, LED8.PLUS1 (PLUS), LED8.PLUS2 (PLUS), R45.1
unnamed: ..LED+, .-1.LED+, LED9.PLUS1 (PLUS), LED9.PLUS2 (PLUS), R47.1
unnamed: /.LED+, /-1.LED+, LED10.PLUS1 (PLUS), LED10.PLUS2 (PLUS), R54.1
unnamed: CAPS-STEPPED.LED+, CAPS-STEPPED.SMDLED+ (LED+), CAPS-TRAD.LED+, CAPS-TRAD.SMDLED+ (LED+), R9.1
unnamed: D113.A, LOPT.MX1 (P0), LOPT1.MX1 (P0)
unnamed: D115.A, LCMD.MX1 (P0)
unnamed: A.LED+, A.SMDLED+ (LED+), R13.1
unnamed: D117.A, SPACE.MX1 (P0)
unnamed: D119.A, RCMD-1U.MX1 (P0), RCMD-TRAD.MX1 (P0)
unnamed: Q.LED+, Q.SMDLED+ (LED+), R14.1
unnamed: D121.A, ROPT-1U.MX1 (P0), ROPT-TRAD.MX1 (P0)
unnamed: R4.2, U3.43 (PE2_(ALE/HWB))
unnamed: D123.A, LEFT.MX1 (P0), RMOD1-TRAD.MX1 (P0)
unnamed: 1.LED+, 1.SMDLED+ (LED+), R15.1
unnamed: D125.A, DOWN.MX1 (P0)
unnamed: D127.A, RIGHT.MX1 (P0), RMOD2-TRAD.MX1 (P0)
unnamed: LCMD.LED+, LCMD.SMDLED+ (LED+), R20.1
unnamed: R18.1, S.LED+, S.SMDLED+ (LED+)
unnamed: R17.1, W.LED+, W.SMDLED+ (LED+)
unnamed: 3.LED+, 3.SMDLED+ (LED+), R24.1
unnamed: E.LED+, E.SMDLED+ (LED+), R23.1
unnamed: D.LED+, D.SMDLED+ (LED+), R22.1
unnamed: C.LED+, C-1.LED+, LED3.PLUS1 (PLUS), LED3.PLUS2 (PLUS), R21.1
unnamed: F.LED+, F.SMDLED+ (LED+), R27.1
unnamed: R.LED+, R.SMDLED+ (LED+), R26.1
unnamed: 4.LED+, 4.SMDLED+ (LED+), R25.1
unnamed: R32.1, T.LED+, T.SMDLED+ (LED+)
unnamed: G.LED+, G.SMDLED+ (LED+), R31.1
unnamed: R29.1, SPACE.LED+, SPACE.SMDLED+ (LED+)
unnamed: H.LED+, H.SMDLED+ (LED+), R36.1
unnamed: R35.1, Y.LED+, Y.SMDLED+ (LED+)
unnamed: 6.LED+, 6.SMDLED+ (LED+), R34.1
unnamed: 7.LED+, 7.SMDLED+ (LED+), R41.1
unnamed: R40.1, U.LED+, U.SMDLED+ (LED+)
unnamed: J.LED+, J.SMDLED+ (LED+), R39.1
unnamed: K.LED+, K.SMDLED+ (LED+), R44.1
unnamed: I.LED+, I.SMDLED+ (LED+), R43.1
unnamed: 9.LED+, 9.SMDLED+ (LED+), R50.1
unnamed: O.LED+, O.SMDLED+ (LED+), R49.1
unnamed: L.LED+, L.SMDLED+ (LED+), R48.1
unnamed: R55.1, ROPT-1U.LED+, ROPT-1U.SMDLED+ (LED+), ROPT-TRAD.LED+, ROPT-TRAD.SMDLED+ (LED+)
unnamed: R53.1, SEMICOL.LED+, SEMICOL.SMDLED+ (LED+)
unnamed: P.LED+, P.SMDLED+ (LED+), R52.1
unnamed: 0.LED+, 0.SMDLED+ (LED+), R51.1
unnamed: -.LED+, -.SMDLED+ (LED+), R60.1
unnamed: R59.1, [.LED+, [.SMDLED+ (LED+)
unnamed: '.LED+, '.SMDLED+ (LED+), R58.1
unnamed: ASHIFT.LED+, ASHIFT.SMDLED+ (LED+), R57.1, RSHIFT-1U.LED+, RSHIFT-1U.SMDLED+ (LED+)
unnamed: LEFT.LED+, LEFT.SMDLED+ (LED+), R56.1, RMOD1-TRAD.LED+, RMOD1-TRAD.SMDLED+ (LED+)
unnamed: DOWN.LED+, DOWN.SMDLED+ (LED+), R65.1
unnamed: ENTER-2U.LED+, ENTER-2U.SMDLED+ (LED+), R63.1
unnamed: R62.1, ].LED+, ].SMDLED+ (LED+)
unnamed: =.LED+, =.SMDLED+ (LED+), R61.1
unnamed: 1U-BS.LED+, 1U-BS.SMDLED+ (LED+), BS.LED+, BS.SMDLED+ (LED+), R69.1
unnamed: R68.1, |.LED+, |.SMDLED+ (LED+)
unnamed: ESC.LED+, ESC.SMDLED+ (LED+), R67.1
unnamed: L3.2, U7.7 (SW)
unnamed: BS-R.MX1 (P0), D1.A
unnamed: R88.2, R89.1
unnamed: R87.2, U6.5 (THERM)
unnamed: R89.2, U6.13 (PROG1)
unnamed: R90.2, U6.12 (PROG3)
unnamed: BLE.34 (P0.16), F.RST.1
unnamed: C10.2, D143.3 (K1K2), U1.1 (IN), U1.3 (EN)
unnamed: BS-R.LED+, BS-R.SMDLED+ (LED+), R81.1
unnamed: U$5.DOUT, U$6.DIN
unnamed: U$6.DOUT, U$7.DIN
unnamed: U$7.DOUT, U$8.DIN
unnamed: U$8.DOUT, U$9.DIN
unnamed: U$9.DOUT, U$10.DIN
unnamed: U$10.DOUT, U$11.DIN
unnamed: U$11.DOUT, U$12.DIN
unnamed: U$13.DOUT, U$14.DIN
unnamed: U$21.DOUT, U$22.DIN
unnamed: U$22.DOUT, U$23.DIN
unnamed: U$14.DOUT, U$15.DIN
unnamed: U$15.DOUT, U$16.DIN
unnamed: U$23.DOUT, U$24.DIN
unnamed: U$24.DOUT, U$25.DIN
unnamed: U$16.DOUT, U$17.DIN
unnamed: U$17.DOUT, U$18.DIN
unnamed: U$18.DOUT, U$19.DIN
unnamed: U$25.DOUT, U$26.DIN
unnamed: U$26.DOUT, U$27.DIN
unnamed: U$19.DOUT, U$20.DIN
unnamed: U$27.DOUT, U$28.DIN
unnamed: R85.2, U$5.DIN
unnamed: U$12.DOUT, U$13.DIN
unnamed: U$20.DOUT, U$21.DIN
OC: Q2.4 (G1), U5.3 (OC)
OD: Q2.5 (G2), U5.1 (OD)
RCMD-LED-ITC1: R46.1, RCMD-LSMD.PLUS, RCMD-LTHT.2 (PLUS), RCMD-LTHT.3 (PLUS)
RIGHT-LED-ITC1: R66.1, RIGHT-LSMD.PLUS, RIGHT-LTHT.2 (PLUS), RIGHT-LTHT.3 (PLUS)
ROW1: D15.C, D16.C, D17.C, D18.C, D19.C, D20.C, D21.C, D22.C, D23.C, D24.C, D25.C, D26.C, D27.C, D28.C, U3.61 (PF0_(ADC0))
ROW2: D29.C, D30.C, D31.C, D32.C, D33.C, D34.C, D35.C, D36.C, D37.C, D38.C, D39.C, D40.C, D41.C, D42.C, U3.60 (PF1_(ADC1))
ROW3: D1.C, D57.C, D58.C, D59.C, D60.C, D61.C, D62.C, D63.C, D64.C, D65.C, D66.C, D67.C, D68.C, D69.C, U3.59 (PF2_(ADC2))
ROW4: D70.C, D84.C, D85.C, D86.C, D87.C, D88.C, D89.C, D90.C, D91.C, D92.C, D93.C, D94.C, D95.C, D96.C, U3.58 (PF3_(ADC3))
ROW5: D111.C, D113.C, D115.C, D117.C, D119.C, D121.C, D123.C, D125.C, D127.C, U3.57 (PF4_(ADC4/TCK))
RST_SW: C1_RST.2, D4.A, R1_RST.1, RST.2, U3.20 (!RESET)
SCK_3.3V: BLE.4 (P0.21), U2.6 (1Y)
SCK_5V: U2.1 (1A), U3.11 ((PCINT1/SCLK)_PB1)
SWCLK: BLE.36 (SWCLK), J2.P$2 (SWCLK)
SWRST_3.3V: BLE.35 (NRESET/SWDIO), J2.P$1 (SWDIO), R80.2, U$1.S
SWRST_5V: R79.2, U3.29 ((ICP1)_PD4), U$1.D
UCAP: C7.2, U3.7 (UCAP)
UG: R85.1, U3.15 ((PCINT5/OC.1A)_PB5)
UP-LED-ITC1: R64.1, TS_SH.LED+, TS_SH.SMDLED+ (LED+), UP-LSMD.PLUS, UP-LTHT.2 (PLUS), UP-LTHT.3 (PLUS)
USB_1_N: R6.2, U3.4 (D-)
USB_1_P: R5.2, U3.5 (D+)
USB_C_N: U4.4 (I/O2_2), USB-C.A7 (DN1), USB-C.B7 (DN2)
USB_C_P: U4.6 (I/O1_2), USB-C.A6 (DP1), USB-C.B6 (DP2)
USB_N: R6.1, U4.3 (I/O2_1)
USB_P: R5.1, U4.1 (I/O1_1)
VBUS: C6.2, F1.1 (IN), U3.8 (VBUS), U4.5 (VBUS), USB-C.A4 (VBUS), USB-C.B4 (VBUS)
VCC: C13.2, C15.2, C16.2, C19.2, C20.2, C21.2, C22.2, C23.2, C24.2, C25.2, C26.2, C27.2, C28.2, C29.2, C30.2, C31.2, C32.2, C33.2, C34.2, C35.2, C36.2, C37.2, C38.2, C39.2, C40.2, C41.2, C42.2, C44.2, C45.2, D4.C, D143.2 (A2), R1_RST.2, R7.2, R8.2, R9.2, R10.2, R11.2, R12.2, R13.2, R14.2, R15.2, R16.2, R17.2, R18.2, R19.2, R20.2, R21.2, R22.2, R23.2, R24.2, R25.2, R26.2, R27.2, R28.2, R29.2, R30.2, R31.2, R32.2, R33.2, R34.2, R35.2, R36.2, R37.2, R38.2, R39.2, R40.2, R41.2, R42.2, R43.2, R44.2, R45.2, R46.2, R47.2, R48.2, R49.2, R50.2, R51.2, R52.2, R53.2, R54.2, R55.2, R56.2, R57.2, R58.2, R59.2, R60.2, R61.2, R62.2, R63.2, R64.2, R65.2, R66.2, R67.2, R68.2, R69.2, R70.2, R78.2, R79.1, R81.2, U3.3 (UVCC), U3.21 (VCC), U3.52 (VCC), U3.64 (AVCC), U7.2 (VOUT), U$5.VCC (VDD), U$6.VCC (VDD), U$7.VCC (VDD), U$8.VCC (VDD), U$9.VCC (VDD), U$10.VCC (VDD), U$11.VCC (VDD), U$12.VCC (VDD), U$13.VCC (VDD), U$14.VCC (VDD), U$15.VCC (VDD), U$16.VCC (VDD), U$17.VCC (VDD), U$18.VCC (VDD), U$19.VCC (VDD), U$20.VCC (VDD), U$21.VCC (VDD), U$22.VCC (VDD), U$23.VCC (VDD), U$24.VCC (VDD), U$25.VCC (VDD), U$26.VCC (VDD), U$27.VCC (VDD), U$28.VCC (VDD)
VCC3.3: BLE.3 (AVDD), BLE.14 (VDD), C11.2, C12.2, D143.1 (A1), R3.2, R80.1, U1.5 (OUT), U2.5 (VCC), U$1.G
VFILTER: C2.2, C3.2, C4.2, L2.2, U6.2 (VPCC), U6.4 (PROG2), U6.9 (!TE), U6.17 (CE), U6.18 (IN), U6.19 (IN)
VMCP: C43.2, L3.1, U6.1 (OUT), U6.20 (OUT), U7.4 (ILIM), U7.6 (EN), U7.8 (VIN)
XTAL1: C8.1, U3.24 (XTAL1), Y1.1
XTAL2: C9.1, U3.23 (XTAL2), Y1.3 (2)

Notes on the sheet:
4.5
5.5
MCU Support
Per-Key LED Subsystem
Power Management Subsystem
Note that 12pF is for a crystal w/ Load Capacitance of 10pF. Part chosen for crystal is 10pF. Adjust if necessary. Cap = 2*CL - 2*C_[stray] where C_[stray] is assumed to be 2pF. Closest common value chosen
Datasheet for FS312F-G gives 100Ω for VCC Resist. Equiv. = 3x 300Ω in Parr.
USB Connector
MDBT40-256v3 BLE Subsystem
RGB Underglow Subsystem
Decoupling Caps
Crystal
Reset
Support Caps
USB Filtering and Protection
Battery Charging
DC-DC Boost Converter
Li-Ion Battery Protection
Battery Connector
Level Shifters
Voltage Regulation
Main MDBT40 Chip
Programming Pads
VBUS is passed through a 500mA fuse followed by a Schottky Diode This creates overcurrent and backflow protection High Frequency EMC is filtered by a ferrite bead and output is smoothed by decoupling capacitors
Battery Level
SMD LED Pick and Place Positions\
These LED's are not electrically connected and are only used to add positions for the Pick-and-Place Centroid file needed for assembly.

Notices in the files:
parts and their libraries:
COPYRIGHT: Copyright (C) 2016 Accelerated Designs. All rights reserved
